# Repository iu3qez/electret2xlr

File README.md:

# electret2xlr

Active adapter that powers an electret microphone from P48 phantom power and presents its signal to a balanced XLR input — no external supply. Built as pcb-as-code with the [`pcb`](https://github.com/diodeinc/pcb) toolchain (Zener language). Designed for a ham-radio shack, so **RF immunity is a first-class requirement**, not an afterthought.

The electronics live in an external **copper-foil enclosure** (Faraday shield) and connect to the sound card through a shielded cable ending in a **flying male XLR plug** (e.g. Neutrik NC3MX).

## How it works

Three stages (~15 passives/actives plus connectors):

1. **Supply (capacitance multiplier).** Phantom 48 V is tapped symmetrically from XLR pins 2/3. An 8.2 V zener (D1) sets a raw reference; R9 47 kΩ + C4 47 µF push the corner below 1 Hz to scrub the zener's avalanche noise; NPN follower Q1 (MMBT3904) buffers it into a clean **VPIP ≈ 7.5 V** rail. Capsule bias comes off VPIP through R10 6.8 kΩ.
2. **Audio (matched class-A followers).** Two PNP emitter followers (MMBT3906): **Q2** (hot) takes the capsule signal (AC-coupled via C2) and modulates the current drawn from pin 2 through R1 7.5 kΩ; **Q3** (cold) is identical but AC-grounded, drawing from pin 3 through R2 10 kΩ. Result: pseudo-balanced ~78 Ω source, ~3 mA/pin symmetric. CB2/CB3 emitter-bypass caps are **1 µF** (not 22 µF — a larger value pushes the HP knee below 1 Hz and defeats the intended ~30 Hz roll-off).
3. **Input.** Capsule solder pads (MIC1) and an optional 3.5 mm TRS jack (J2), preceded by a π anti-RF filter (CIN 220 pF + FB1 ferrite + RIN 100 Ω) — the mic cable is the main antenna, so this is the front line against HF detection on the capsule FET.

Extra RF defenses: CP2/CP3 (100 pF C0G, pin2/pin3→GND), CSH (1 nF, shell→GND), and a 4-layer board with internal ground planes in addition to the copper enclosure.

## Key figures (SPICE-verified)

From `docs/sim-results.md` (ngspice via `pcb sim`):

| Quantity | Simulated | Target |
|---|---|---|
| V(VPIP) | 7.49 V | 7.0–8.0 V |
| V(MICOUT) | 4.09 V | 3–5 V |
| Current per pin (P2 / P3) | 3.00 / 3.13 mA | 2.5–3.5 mA |
| P2 vs P3 imbalance | 4.4 % | < 10 % |
| Flatness 100 Hz–20 kHz | 0.44 dB | ±1 dB |
| Low −3 dB roll-off | ≈ 30.6 Hz | 20–60 Hz |

The differential output phase at 1 kHz is ≈ −179° (inverted vs the conventional sign) — a known trait shared with the reference design, left as a bench-verification item, not fixed here.

## Build

Prerequisites: **`pcb`** (Rust binary, not on PyPI) and **KiCad 10.x** (only needed for `pcb layout`).

```bash
curl -fsSL https://raw.githubusercontent.com/diodeinc/pcb/main/install.sh | bash
export PATH="$HOME/.local/bin:$PATH"        # pcbc 0.4.7 used here
git clone https://github.com/iu3qez/electret2xlr && cd electret2xlr
pcb build electret2xlr.zen                  # 32 components, no errors
pcb layout electret2xlr.zen                 # open/update layout in KiCad
```

Footprints and symbols are **vendored** (`footprints/`, `symbols/`), so a clean clone builds offline — **no `pcb auth login` or online registry needed**. KiCad 10.x install: official AppImage (no sudo), Flatpak `org.kicad.KiCad`, or a distro package with 10.x.

**Placement and routing are left to the user.** The imported `layout/layout.kicad_pcb` (4-layer, 1.6 mm, 50×40 mm outline) has components at netlist-import coordinates. DRC therefore reports the 51 unrouted nets plus a few overlap violations from `J1` auto-dropped onto the C4/Q2/J2 cluster — both clear once parts are placed.

Optional SPICE re-run (needs `ngspice`):

```bash
NGSPICE=/path/to/ngspice pcb sim electret2xlr.zen --config sim_mode=true --setup testbench/setup_dc_ac.cir -v
```

`sim_mode=true` drops the two capsule test points (no stdlib SPICE model); a normal `pcb build` keeps them as real pads.

## Wiring

- **J1 → flying XLR** (`footprints/J1_XLR3_WirePads.kicad_mod`, 3 THT pads): pin1 = GND/shield, pin2 = hot (P2), pin3 = cold (P3). Solder the shielded cable here; wire the other end to a male XLR plug (pin1 shield, pin2 +, pin3 −). Bond the copper enclosure to GND at pin 1.
- **Capsule** on MIC1 pads (2.54 mm pitch): signal/bias to one pad, GND to the other; observe the capsule's own polarity.
- **Jack J2** (optional, on the enclosure): tip = signal/bias, ring bridged to tip, sleeve = GND. Smartphone TRRS headsets need an external TRRS→TRS adapter.
- **SHELL pad:** the copper-foil contact (net `SHELL`, where CSH lands) is a hand-drawn copper feature tied to GND, not a netlist part — so `pcb build` emits an expected single-pin-net ERC warning for `SHELL`.

## Attribution & license

Topology inspired by [tphakala/p48-pip-adapter](https://github.com/tphakala/p48-pip-adapter). That project's CC BY-NC 4.0 covers its concrete design (layout, gerbers, docs), not the circuit topology — a widely published functional idea. This repo's Zener source, layout, and docs are written from scratch, so no license constraint is inherited; attribution here is a courtesy.

## Reference docs

- `docs/superpowers/specs/2026-07-15-electret2xlr-design.md` — full design spec
- `docs/sim-results.md` — SPICE verification (DC + AC)
- `docs/meccanica.md` — mechanical fit study (historical: in-connector mount, superseded by the external enclosure)
- `docs/bom.md` — bill of materials

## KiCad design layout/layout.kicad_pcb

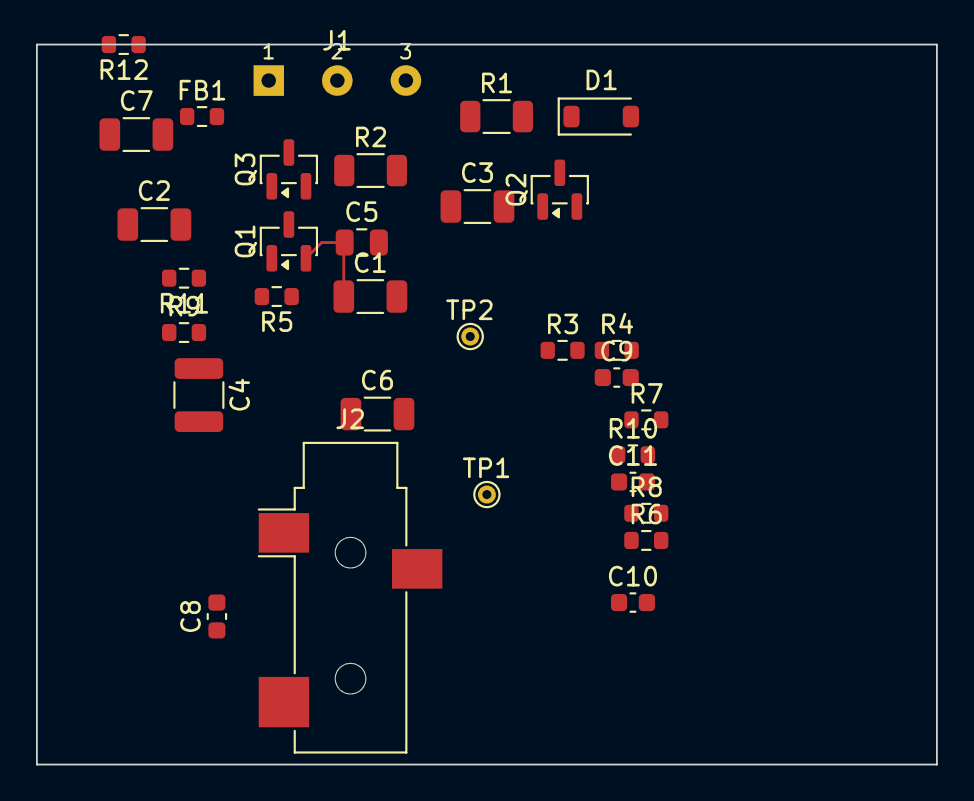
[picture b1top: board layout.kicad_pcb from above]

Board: 4 copper layers, 50.0 x 40.0 mm, 32 parts (0 on the bottom side), 15 nets.

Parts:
C1, C2, C3: 22uF 25V X5R; C_1206_3216Metric
C4: 47uF 25V; C_1210_3225Metric
C5: GRM21BZ71E106KE15K; C_0805_2012Metric
C6, C7: 1uF 50V X7R; C_1206_3216Metric
C8: 220pF C0G; C_0603_1608Metric
C9, C10: 100pF 100V C0G; C_0603_1608Metric
C11: 1nF 100V C0G; C_0603_1608Metric
D1: 8.2V Zener 500mW; D_SOD-123
FB1: 600 500mA 100MHz; R_0603_1608Metric
J1: ?; J1_XLR3_WirePads
J2: SJ-3523-SMT-TR; Jack_3.5mm_CUI_SJ-3523-SMT_Horizontal
Q1: MMBT3904; SOT-23
Q2, Q3: MMBT3906; SOT-23
R1: 7.5k; R_1206_3216Metric
R2: 10k; R_1206_3216Metric
R3, R4, R6, R7: ERJ-3EKF1003V; R_0603_1608Metric
R5, R11: ERJ-3EKF47R0V; R_0603_1608Metric
R8: ERJ-3EKF1001V; R_0603_1608Metric
R9: ERJ-3EKF4702V; R_0603_1608Metric
R10: ERJ-3EKF6801V; R_0603_1608Metric
R12: ERJ-3EKF1000V; R_0603_1608Metric
TP1, TP2: ?; TestPoint_THTPad_D1.0mm_Drill0.5mm

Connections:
GND: C1.2, C3.2, C4.2, C5.2, C8.2, C9.2, C10.2, C11.2, D1.2, J1.1, J2.S, Q2.3, Q3.3, R4.2, R7.2, TP2.1
MICF: FB1.2, R12.1
MICIN: C8.1, FB1.1, J2.R, J2.T, TP1.1
MICOUT: C2.1, R10.2, R12.2
NB2: C6.2, R5.1
NB3: C7.2, R11.1
P2: C9.1, J1.2, R1.1, R5.2
P3: C10.1, J1.3, Q1.3, R2.1, R9.1, R11.2
Q1B: Q1.1, R8.2
Q2B: C2.2, Q2.1, R3.2, R4.1
Q2E: C6.1, Q2.2, R1.2
Q3B: C3.1, Q3.1, R6.2, R7.1
Q3E: C7.1, Q3.2, R2.2
VPIP: C1.1, C5.1, Q1.2, R3.1, R6.1, R10.1
VREF: C4.1, D1.1, R8.1, R9.2
